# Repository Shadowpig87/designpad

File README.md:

# designpad
This is a hackpad that I made for the hackclub/stardance project, so I can more easily design my pcbs and other things on CAD softwares, it has an OLED screen, a 3x3 matrix , and a rotary encoder!

The bom can be found here --- https://github.com/Shadowpig87/designpad/blob/main/designboardV1/production/bom.csv

Why did I make this board??

I really like desiginig pcbs and other models in different CAD models, and with this hackpad, after assigning all of the shortucts, I think I can really improve on my skills
Also desiging this hackpad was a ton of fun!

The reason I didn't put a case for this pcb is cause I already have some plans on how to make one, not 3D printing

Features:
128x32 OLED display
EC11 Rotary Encoder(for zooming in ofc)
9x Cherry MX Switches
9x 1N4148 DO-35 Diodes
9x DSA Keycaps

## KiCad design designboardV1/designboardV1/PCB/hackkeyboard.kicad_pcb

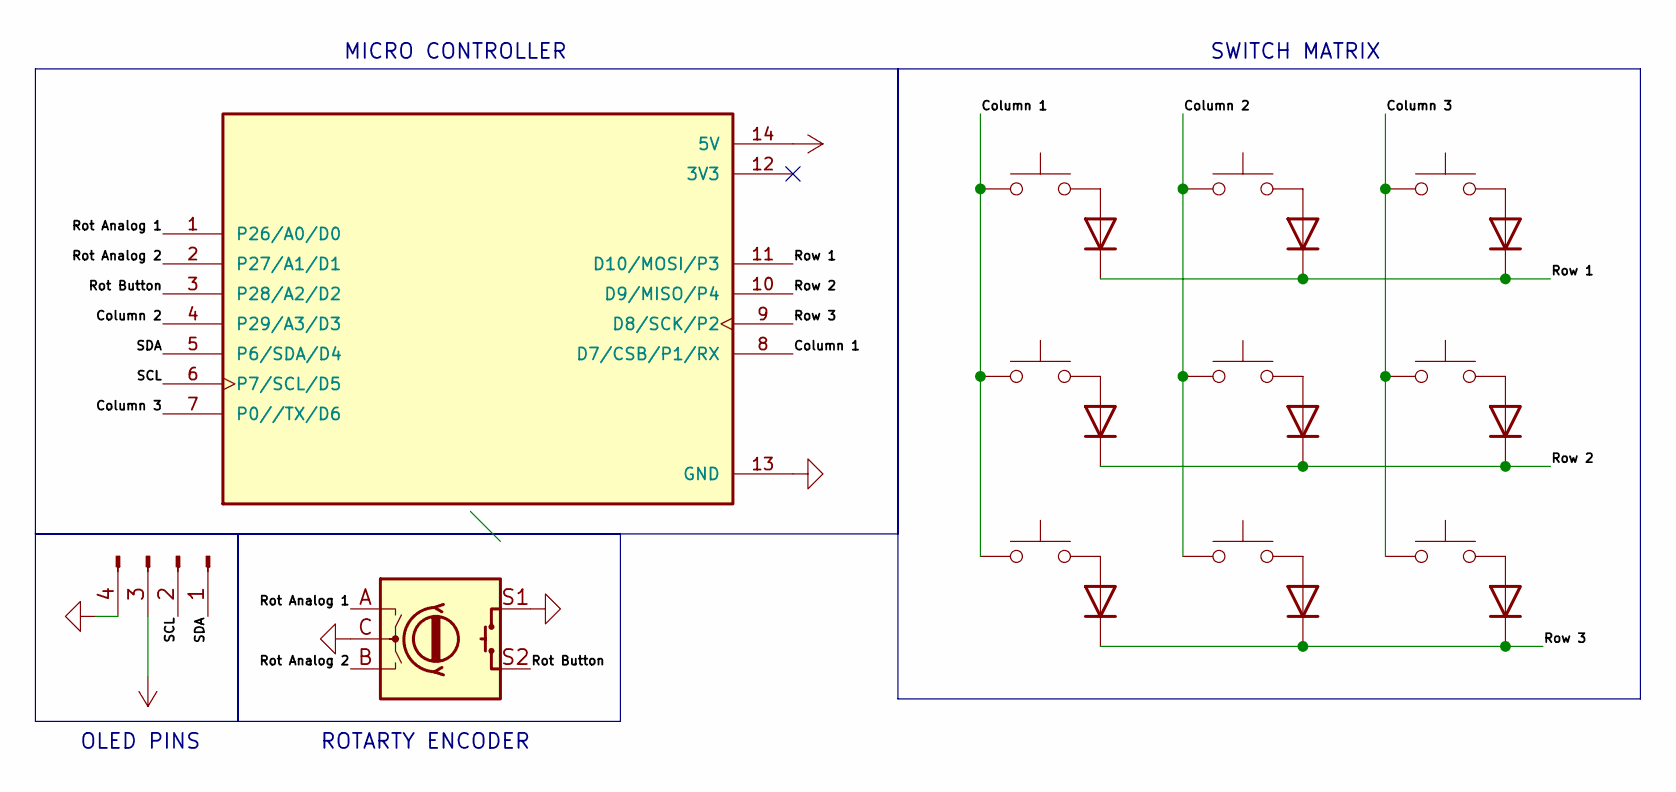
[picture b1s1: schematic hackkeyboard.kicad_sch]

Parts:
D1, D2, D3, D4, D5, D6, D7, D8, D9: 1N4148WT; D_DO-35_SOD27_P7.62mm_Horizontal
J1: Conn_01x04_Pin; PinHeader_1x04_P2.54mm_Vertical
SW1, SW2, SW3, SW4, SW6, SW7, SW8, SW9, SW10: SW_Push; SW_Cherry_MX_1.00u_PCB
SW5: RotaryEncoder_Switch; RotaryEncoder_Alps_EC11E-Switch_Vertical_H20mm
U1: 102010428; MODULE_102010428; PARTREV 1.3

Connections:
+5V: J1.3, U1.14 (5V)
/Column 1: SW1.2, SW3.1, SW6.1, U1.8 (D7/CSB/P1/RX)
/Column 2: SW2.2, SW7.1, SW10.1, U1.4 (P29/A3/D3)
/Column 3: SW4.1, SW8.1, SW9.1, U1.7 (P0//TX/D6)
/Rot Analog 1: SW5.A, U1.1 (P26/A0/D0)
/Rot Analog 2: SW5.B, U1.2 (P27/A1/D1)
/Rot Button: SW5.S2, U1.3 (P28/A2/D2)
/Row 1: D7.1 (K), D8.1 (K), D9.1 (K), U1.11 (D10/MOSI/P3)
/Row 2: D1.1 (K), D2.1 (K), D3.1 (K), U1.10 (D9/MISO/P4)
/Row 3: D4.1 (K), D5.1 (K), D6.1 (K), U1.9 (D8/SCK/P2)
/SCL: J1.2, U1.6 (P7/SCL/D5)
/SDA: J1.1, U1.5 (P6/SDA/D4)
GND: J1.4, SW5.C, SW5.S1, U1.13 (GND)
unnamed: D1.2 (A), SW1.1
unnamed: D2.2 (A), SW2.1
unnamed: D3.2 (A), SW4.2
unnamed: D4.2 (A), SW6.2
unnamed: D5.2 (A), SW7.2
unnamed: D6.2 (A), SW8.2
unnamed: D7.2 (A), SW9.2
unnamed: D8.2 (A), SW10.2
unnamed: D9.2 (A), SW3.2

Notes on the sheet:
ROTARTY ENCODER
OLED PINS
SWITCH MATRIX
MICRO CONTROLLER

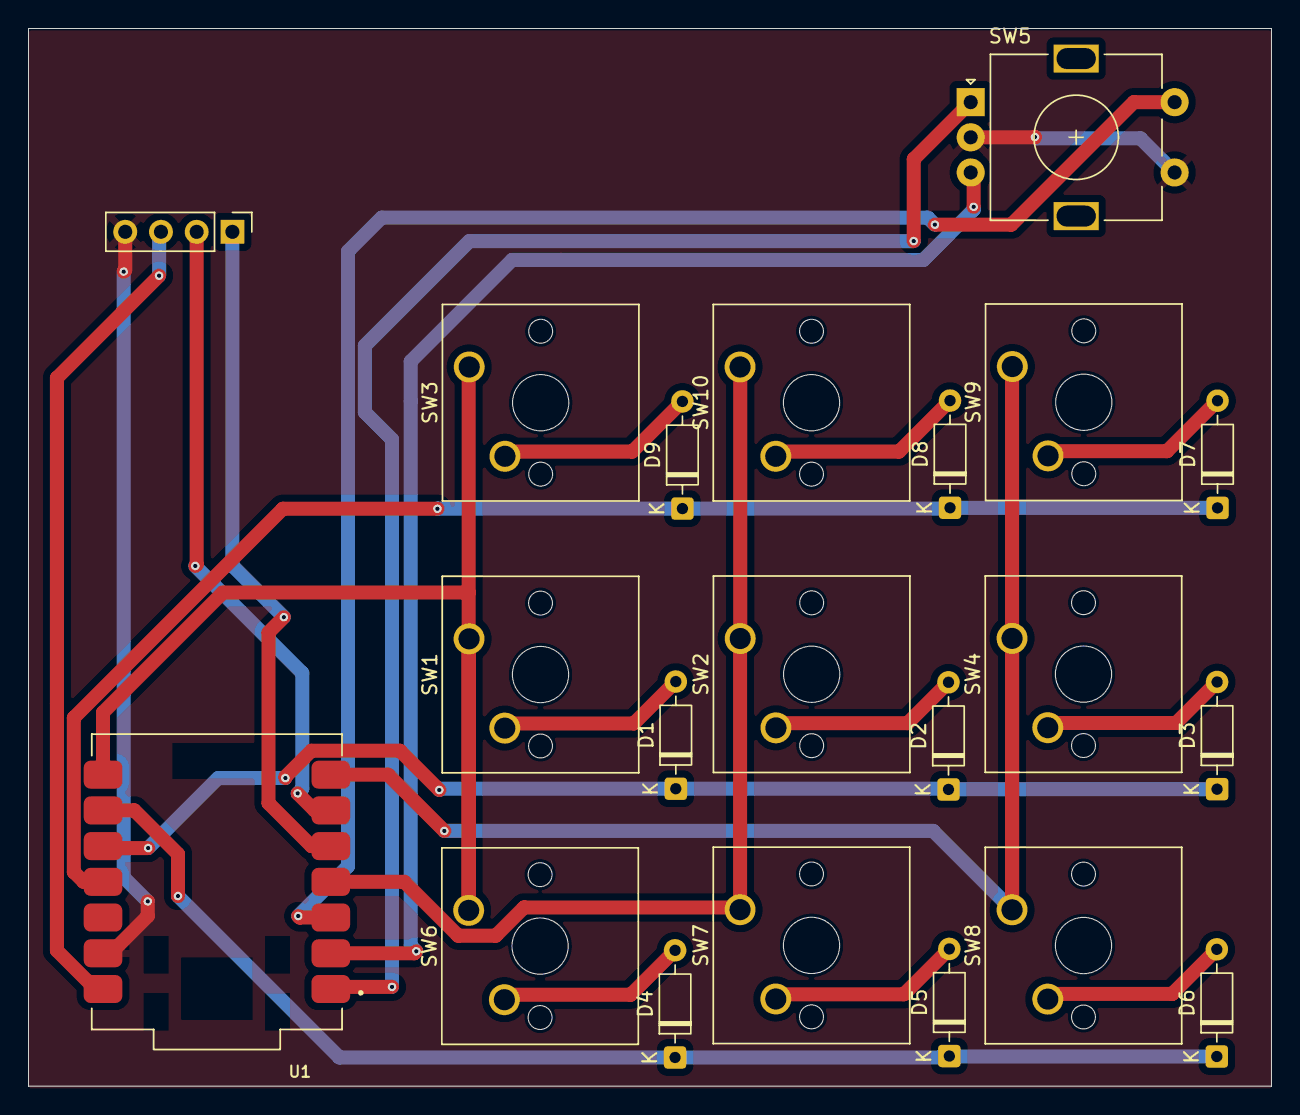
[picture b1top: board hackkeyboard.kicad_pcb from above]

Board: 2 copper layers, 88.4 x 75.2 mm, 21 parts (0 on the bottom side), 22 nets.

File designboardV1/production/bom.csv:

"Id";"Designator";"Footprint";"Quantity";"Designation";"Supplier and ref";
1;"SW9,SW7,SW6,SW1,SW4,SW8,SW3,SW2,SW10";"SW_Cherry_MX_1.00u_PCB";9;"SW_Push";;;
2;"D3,D2,D5,D1,D4,D6,D8,D9,D7";"D_DO-35_SOD27_P7.62mm_Horizontal";9;"1N4148WT";;;
3;"SW5";"RotaryEncoder_Alps_EC11E-Switch_Vertical_H20mm";1;"RotaryEncoder_Switch";;;
4;"U1";"MODULE_102010428";1;"102010428";;;
5;"J1";"PinHeader_1x04_P2.54mm_Vertical";1;"Conn_01x04_Pin";;;
